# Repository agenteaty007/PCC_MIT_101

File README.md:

PCC_MIT_101
===========

Introduction to Robotics class at Pasadena City College.

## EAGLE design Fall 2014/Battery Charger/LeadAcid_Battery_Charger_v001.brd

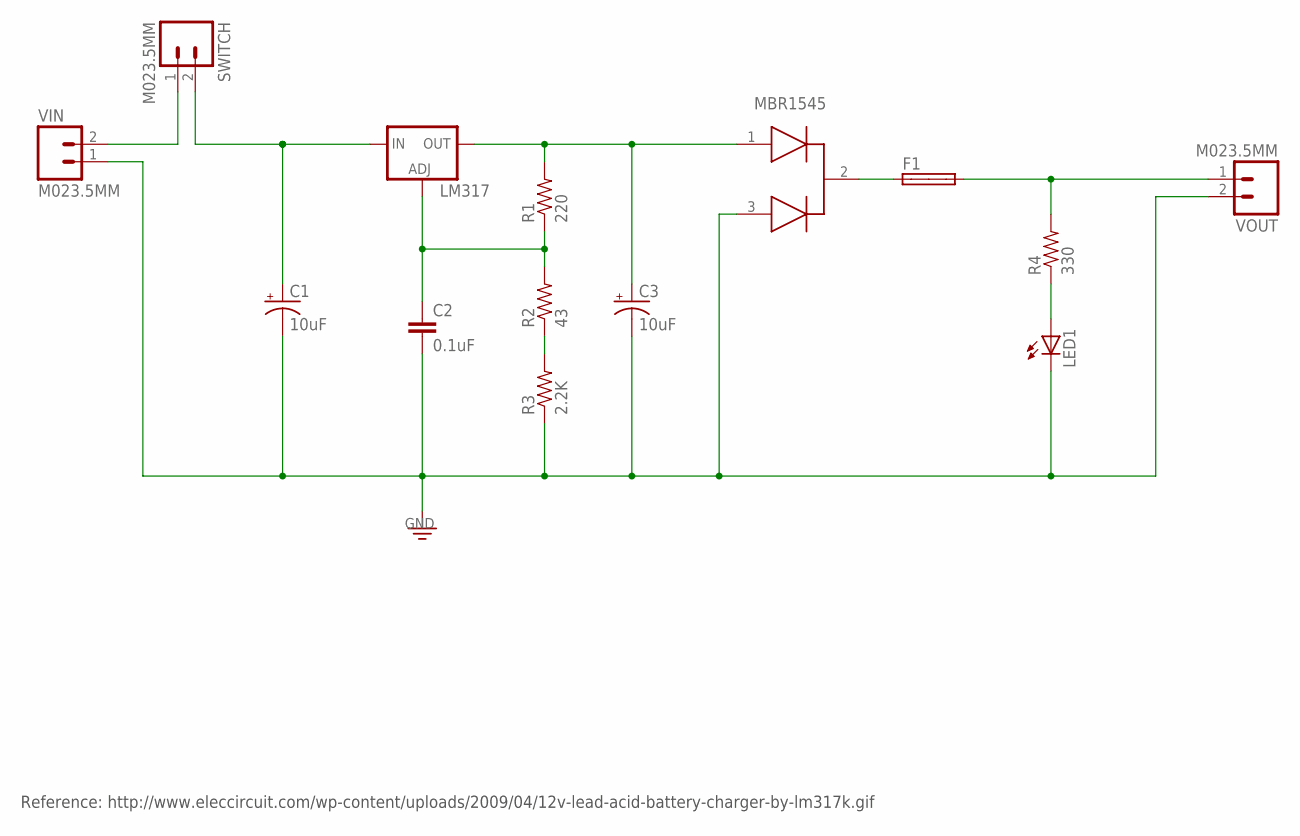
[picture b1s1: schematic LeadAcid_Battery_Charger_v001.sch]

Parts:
C1, C3: 10uF; CPOL-RADIAL-10UF-25V
C2: 0.1uF; CAP-PTH-5MM
F1: SHK20L
LED1: LED3MM
LM317: LM317TS; 317TS
MBR1545: MBR1545; TO-220
R1: 220; AXIAL-0.4
R2: 43; AXIAL-0.4
R3: 2.2K; AXIAL-0.4
R4: 330; AXIAL-0.4
SWITCH: M023.5MM; SCREWTERMINAL-3.5MM-2
VIN: M023.5MM; SCREWTERMINAL-3.5MM-2
VOUT: M023.5MM; SCREWTERMINAL-3.5MM-2

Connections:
GND: C1.2 (-), C2.2, C3.2 (-), LED1.K (C), MBR1545.3, R3.P$1 (1), VIN.1, VOUT.2
unnamed: F1.1A, MBR1545.2
unnamed: C3.1 (+), LM317.2 (OUT), MBR1545.1, R1.P$2 (2)
unnamed: F1.2A, R4.P$2 (2), VOUT.1
unnamed: R2.P$1 (1), R3.P$2 (2)
unnamed: C2.1, LM317.1 (ADJ), R1.P$1 (1), R2.P$2 (2)
unnamed: LED1.A, R4.P$1 (1)
unnamed: SWITCH.1, VIN.2
unnamed: C1.1 (+), LM317.3 (IN), SWITCH.2

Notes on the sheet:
Reference: http://www.eleccircuit.com/wp-content/uploads/2009/04/12v-lead-acid-battery-charger-by-lm317k.gif

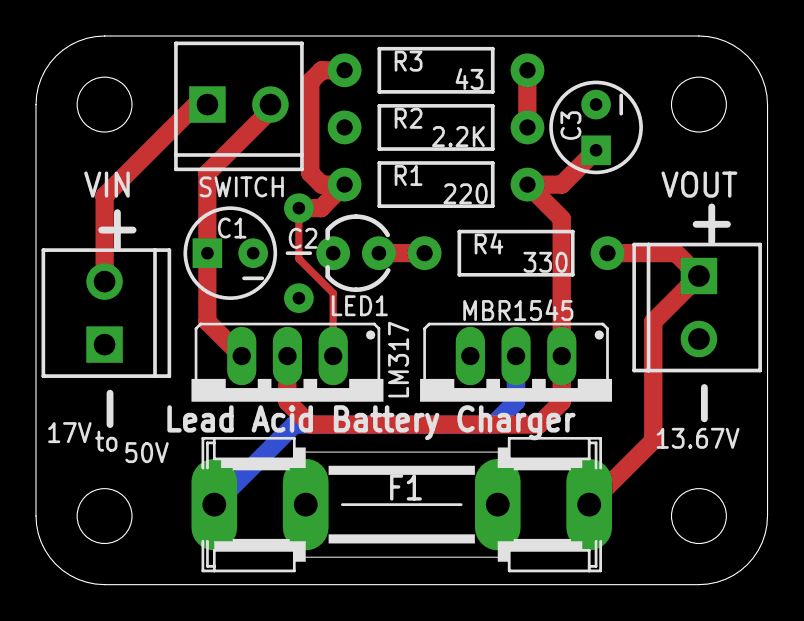
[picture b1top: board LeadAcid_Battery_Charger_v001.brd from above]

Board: 2 copper layers, 40.6 x 30.5 mm, 18 parts (0 on the bottom side), 9 nets.

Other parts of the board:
U$1, U$3, U$4, U$5: STAND-OFF-TIGHT

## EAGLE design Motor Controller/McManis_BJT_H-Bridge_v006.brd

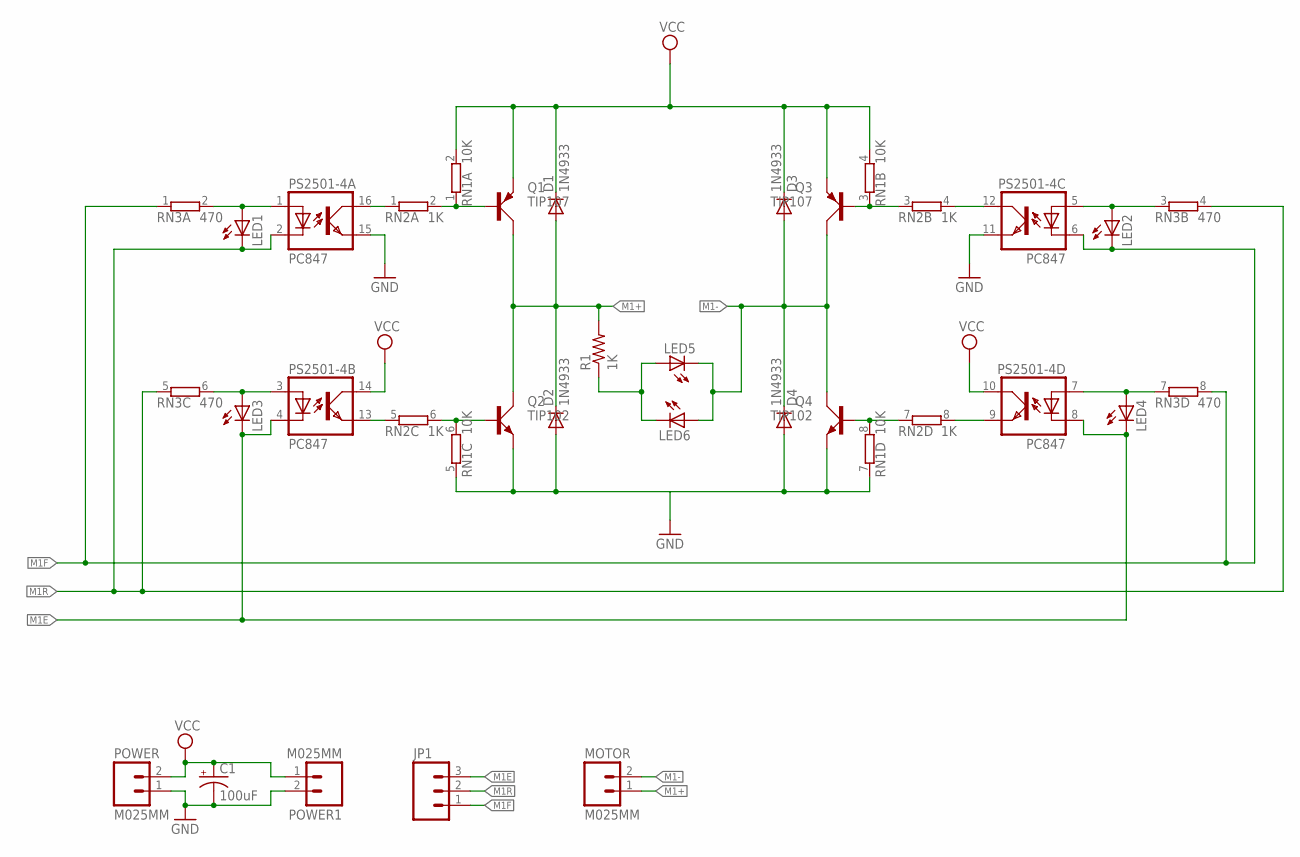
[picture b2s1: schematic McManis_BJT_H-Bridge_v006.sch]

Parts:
C1: 100uF; CPOL-RADIAL-100UF-25V
D1, D2, D3, D4: 1N4933; DO41-10
JP1: M03PTH; 1X03
LED1, LED2, LED3, LED4, LED5, LED6: LED3MM
MOTOR: M025MM; SCREWTERMINAL-5MM-2
POWER, POWER1: M025MM; SCREWTERMINAL-5MM-2
PS2501-4: PC847; DIL16
Q1, Q3: TIP107; TO220AV
Q2, Q4: TIP102; TO220AV
R1: 1K; AXIAL-0.4
RN1: 10K; SIL8
RN2: 1K; SIL8
RN3: 470; SIL8

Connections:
GND: C1.2 (-), D2.A, D4.A, POWER.1, POWER1.2, PS2501-4.11 (EMIT), PS2501-4.15 (EMIT), Q2.E, Q4.E, RN1.5 (1), RN1.7 (1)
M1+: D1.A, D2.C, MOTOR.1, Q1.C, Q2.C, R1.P$2 (2)
M1-: D3.A, D4.C, LED5.K (C), LED6.A, MOTOR.2, Q3.C, Q4.C
M1E: JP1.3, LED3.K (C), LED4.K (C), PS2501-4.4 (C), PS2501-4.8 (C)
M1F: JP1.1, LED2.K (C), PS2501-4.6 (C), RN3.1, RN3.8 (2)
M1R: JP1.2, LED1.K (C), PS2501-4.2 (C), RN3.4 (2), RN3.5 (1)
unnamed: Q2.B, RN1.6 (2), RN2.6 (2)
unnamed: Q1.B, RN1.1, RN2.2
unnamed: PS2501-4.16 (COL), RN2.1
unnamed: PS2501-4.13 (EMIT), RN2.5 (1)
unnamed: Q4.B, RN1.8 (2), RN2.7 (1)
unnamed: Q3.B, RN1.3 (1), RN2.3 (1)
unnamed: PS2501-4.9 (EMIT), RN2.8 (2)
unnamed: PS2501-4.12 (COL), RN2.4 (2)
unnamed: LED1.A, PS2501-4.1 (A), RN3.2
unnamed: LED3.A, PS2501-4.3 (A), RN3.6 (2)
unnamed: LED4.A, PS2501-4.7 (A), RN3.7 (1)
unnamed: LED2.A, PS2501-4.5 (A), RN3.3 (1)
unnamed: LED5.A, LED6.K (C), R1.P$1 (1)
VCC: C1.1 (+), D1.C, D3.C, POWER.2, POWER1.1, PS2501-4.10 (COL), PS2501-4.14 (COL), Q1.E, Q3.E, RN1.2, RN1.4 (2)

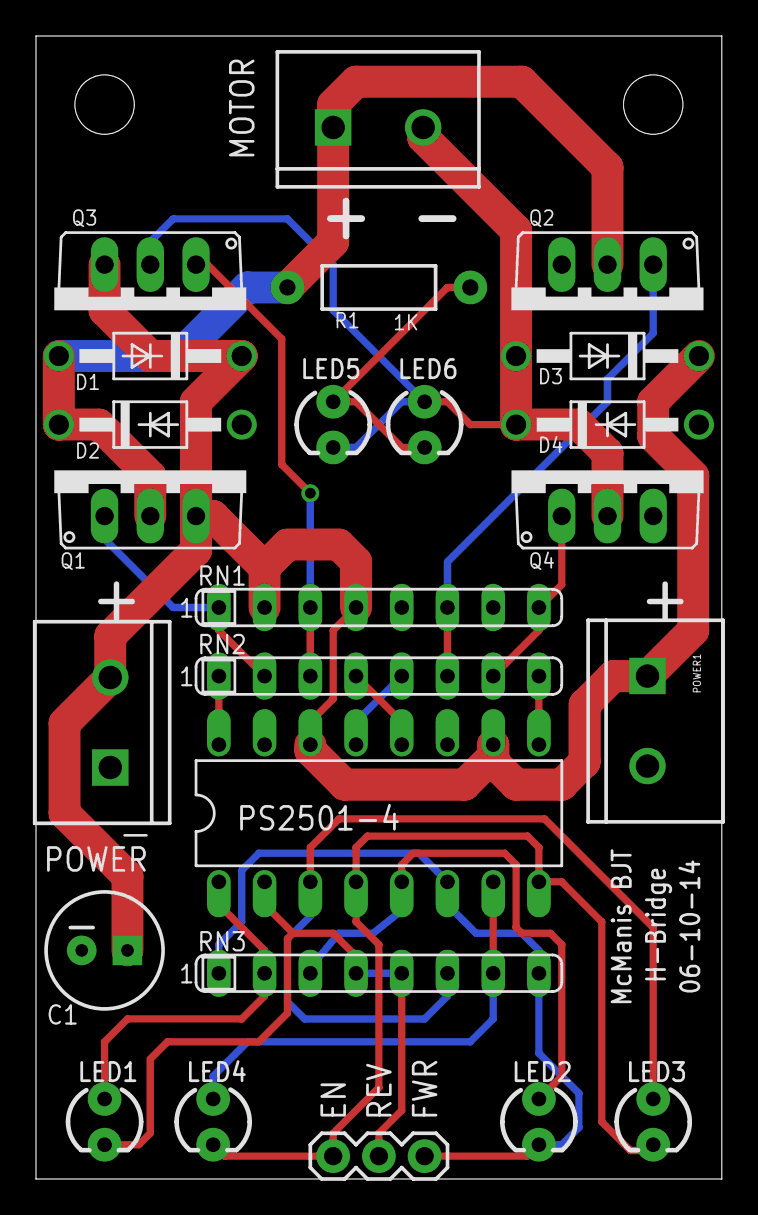
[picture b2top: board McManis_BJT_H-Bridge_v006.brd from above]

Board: 2 copper layers, 38.1 x 63.5 mm, 26 parts (0 on the bottom side), 20 nets.

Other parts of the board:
U$1, U$2: STAND-OFF

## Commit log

2014-09-18 first commit
    Adding H-Bridge (v006), motor controller.
    Adding Battery Charger.
2014-09-18 very brief description
2015-05-07 adding documentation
    Subdividing through Development, Fall 2013, and Spring 2014 folders
    Adding documentation

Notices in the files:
parts and their libraries:
SparkFun-Passives: Licensing: CC v3.0 Share-Alike You are welcome to use this library for commercial purposes.
